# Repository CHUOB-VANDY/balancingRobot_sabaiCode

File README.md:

# balancingRobot_sabaiCode
This hardware development is based on STM32F031C6

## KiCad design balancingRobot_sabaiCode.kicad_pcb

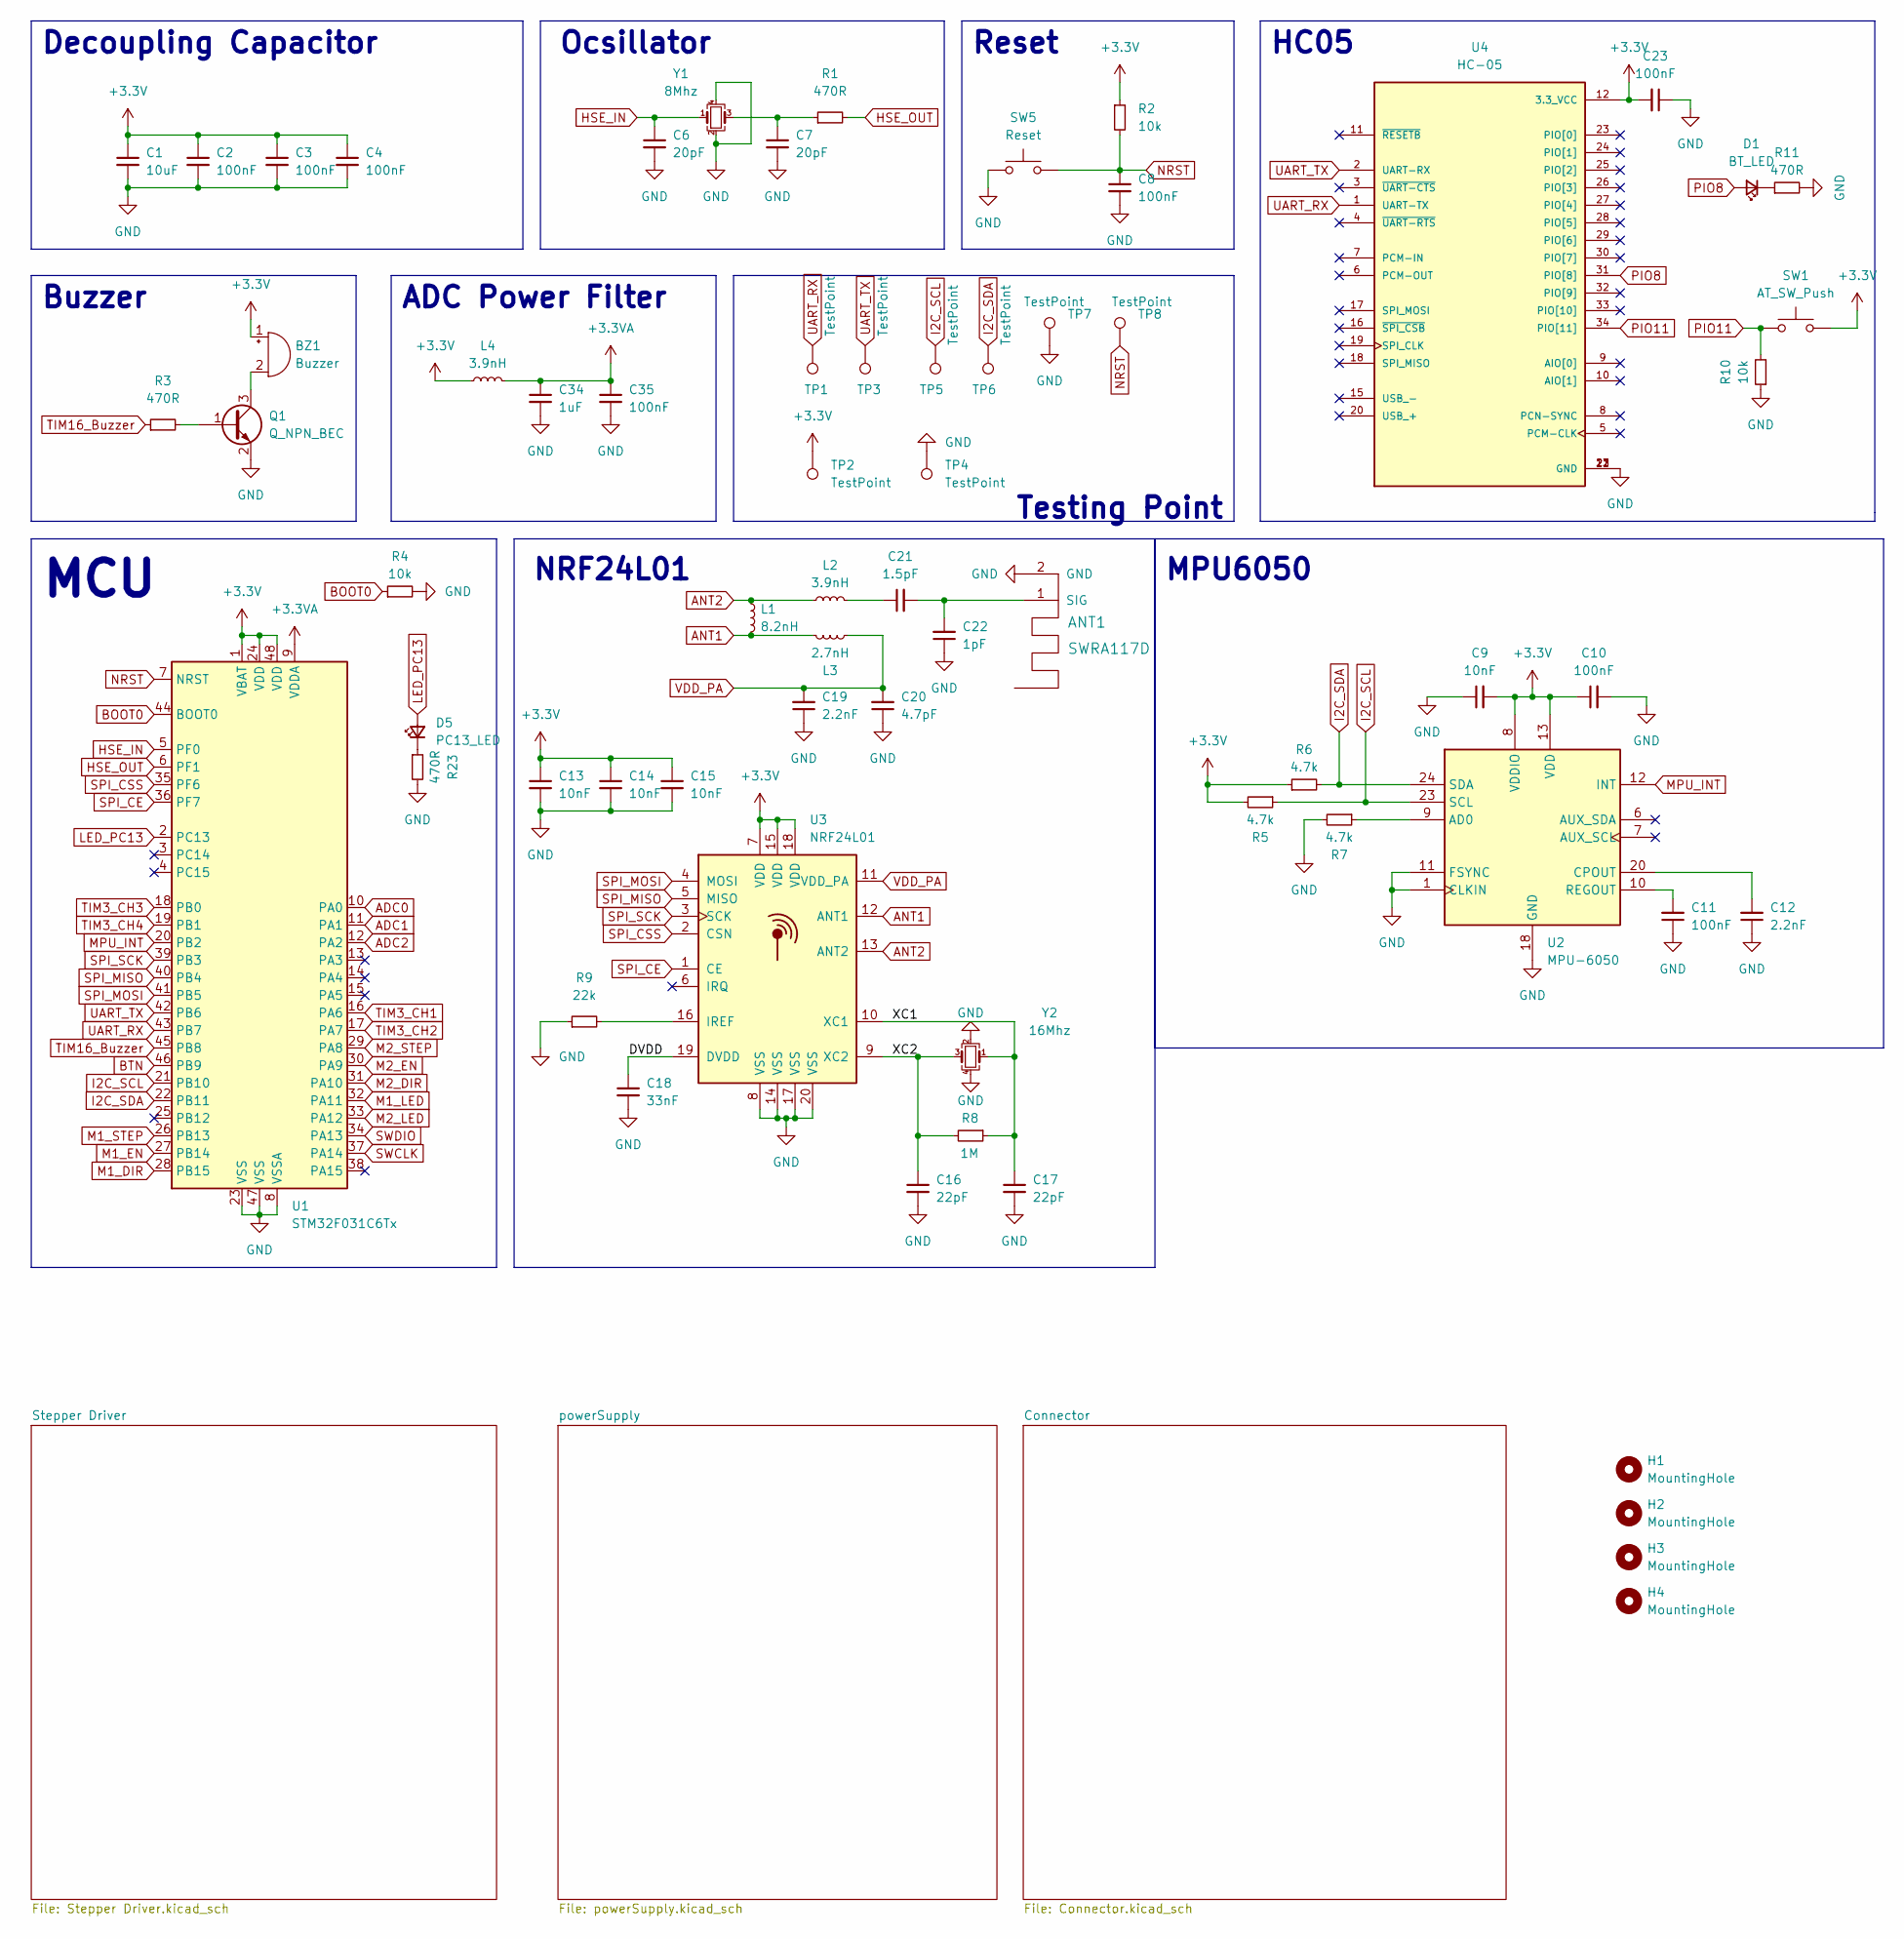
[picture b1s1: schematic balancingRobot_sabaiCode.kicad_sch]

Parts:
ANT1: SWRA117D; Texas_SWRA117D_2.4GHz_Left
BZ1: Buzzer; Buzzer_12x9.5RM7.6
C1: 10uF; C_0805_2012Metric
C2, C3, C4, C8, C10, C11, C23, C35: 100nF; C_0603_1608Metric
C6, C7: 20pF; C_0603_1608Metric
C9, C13, C14, C15: 10nF; C_0603_1608Metric
C12, C19: 2.2nF; C_0603_1608Metric
C16, C17: 22pF; C_0603_1608Metric
C18: 33nF; C_0603_1608Metric
C20: 4.7pF; C_0603_1608Metric
C21: 1.5pF; C_0603_1608Metric
C22: 1pF; C_0603_1608Metric
C34: 1uF; C_0603_1608Metric
D1: BT_LED; LED_0603_1608Metric
D5: PC13_LED; LED_0603_1608Metric
H1, H2, H3, H4: MountingHole; MountingHole_3mm_Pad_Via
L1: 8.2nH; L_0603_1608Metric
L2, L4: 3.9nH; L_0603_1608Metric
L3: 2.7nH; L_0603_1608Metric
Q1: Q_NPN_BEC; SOT-23
R1, R3, R11, R23: 470R; R_0603_1608Metric
R2, R4, R10: 10k; R_0603_1608Metric
R5, R6, R7: 4.7k; R_0603_1608Metric
R8: 1M; R_0603_1608Metric
R9: 22k; R_0603_1608Metric
SW1: AT_SW_Push; SW_SPST_TL3342
SW5: Reset; SW_SPST_TL3342
TP1, TP2, TP3, TP4, TP5, TP6, TP7, TP8: TestPoint; TestPoint_Pad_D1.0mm
U1: STM32F031C6Tx; LQFP-48_7x7mm_P0.5mm
U2: MPU-6050; InvenSense_QFN-24_4x4mm_P0.5mm
U3: NRF24L01; QFN-20-1EP_4x4mm_P0.5mm_EP2.5x2.5mm
U4: HC-05; XCVR_HC-05; PARTREV v1.0
Y1: 8Mhz; Crystal_SMD_3225-4Pin_3.2x2.5mm
Y2: 16Mhz; Crystal_SMD_3225-4Pin_3.2x2.5mm

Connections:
+3.3VA: C34.1, C35.1, L4.2, U1.9 (VDDA)
+3V3: BZ1.1 (-), C1.1, C2.1, C3.1, C4.1, C9.2, C10.1, C13.1, C14.1, C15.1, C23.2, L4.1, R2.1, R5.2, R6.1, SW1.2, TP2.1, U1.1 (VBAT), U1.24 (VDD), U1.48 (VDD), U2.8 (VDDIO), U2.13 (VDD), U3.7 (VDD), U3.15 (VDD), U3.18 (VDD), U4.12 (3.3_VCC); also elsewhere on the board
/DVDD: C18.1, U3.19 (DVDD)
/XC1: C17.1, R8.1, U3.10 (XC1), Y2.1
/XC2: C16.1, R8.2, U3.9 (XC2), Y2.3
ADC0: U1.10 (PA0); also elsewhere on the board
ADC1: U1.11 (PA1); also elsewhere on the board
ADC2: U1.12 (PA2); also elsewhere on the board
ANT1: L1.2, L3.2, U3.12 (ANT1)
ANT2: L1.1, L2.1, U3.13 (ANT2)
BOOT0: R4.1, U1.44 (BOOT0)
BTN: U1.46 (PB9); also elsewhere on the board
GND: ANT1.2 (GND), C1.2, C2.2, C3.2, C4.2, C6.2, C7.2, C8.2, C9.1, C10.2, C11.1, C12.1, C13.2, C14.2, C15.2, C16.2, C17.2, C18.2, C19.1, C20.1, C22.1, C23.1, C34.2, C35.2, Q1.2 (E), R4.2, R7.2, R9.1, R10.1, R11.2, R23.2, SW5.1, TP4.1, TP7.1, U1.8 (VSSA), U1.23 (VSS), U1.47 (VSS), U2.1 (CLKIN), U2.11 (FSYNC), U2.18 (GND), U3.8 (VSS), U3.14 (VSS), U3.17 (VSS), U3.20 (VSS), U4.13 (GND), U4.21 (GND), U4.22 (GND), Y1.2, Y1.4, Y2.2, Y2.4; also elsewhere on the board
HSE_IN: C6.1, U1.5 (PF0), Y1.1
HSE_OUT: R1.2, U1.6 (PF1)
I2C_SCL: R5.1, TP5.1, U1.21 (PB10), U2.23 (SCL); also elsewhere on the board
I2C_SDA: R6.2, TP6.1, U1.22 (PB11), U2.24 (SDA); also elsewhere on the board
LED_PC13: D5.2 (A), U1.2 (PC13)
M1_DIR: U1.28 (PB15); also elsewhere on the board
M1_EN: U1.27 (PB14); also elsewhere on the board
M1_LED: U1.32 (PA11); also elsewhere on the board
M1_STEP: U1.26 (PB13); also elsewhere on the board
M2_DIR: U1.31 (PA10); also elsewhere on the board
M2_EN: U1.30 (PA9); also elsewhere on the board
M2_LED: U1.33 (PA12); also elsewhere on the board
M2_STEP: U1.29 (PA8); also elsewhere on the board
MPU_INT: U1.20 (PB2), U2.12 (INT)
NRST: C8.1, R2.2, SW5.2, TP8.1, U1.7 (NRST)
unnamed: ANT1.1 (SIG), C21.2, C22.2
unnamed: BZ1.2 (+), Q1.3 (C)
unnamed: C7.1, R1.1, Y1.3
unnamed: C11.2, U2.10 (REGOUT)
unnamed: C12.2, U2.20 (CPOUT)
unnamed: C21.1, L2.2
unnamed: D1.1 (K), R11.1
unnamed: D5.1 (K), R23.1
unnamed: Q1.1 (B), R3.2
unnamed: R7.1, U2.9 (AD0)
unnamed: R9.2, U3.16 (IREF)
PIO8: D1.2 (A), U4.31 (PIO[8])
PIO11: R10.2, SW1.1, U4.34 (PIO[11])
SPI_CE: U1.36 (PF7), U3.1 (CE)
SPI_CSS: U1.35 (PF6), U3.2 (CSN)
SPI_MISO: U1.40 (PB4), U3.5 (MISO)
SPI_MOSI: U1.41 (PB5), U3.4 (MOSI)
SPI_SCK: U1.39 (PB3), U3.3 (SCK)
SWCLK: U1.37 (PA14); also elsewhere on the board
SWDIO: U1.34 (PA13); also elsewhere on the board
TIM3_CH1: U1.16 (PA6); also elsewhere on the board
TIM3_CH2: U1.17 (PA7); also elsewhere on the board
TIM3_CH3: U1.18 (PB0); also elsewhere on the board
TIM3_CH4: U1.19 (PB1); also elsewhere on the board
TIM16_Buzzer: R3.1, U1.45 (PB8)
UART_RX: TP1.1, U1.43 (PB7), U4.1 (UART-TX)
UART_TX: TP3.1, U1.42 (PB6), U4.2 (UART-RX)
VDD_PA: C19.2, C20.2, L3.1, U3.11 (VDD_PA)

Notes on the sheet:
Buzzer
NRF24L01
Decoupling Capacitor
HC05
Reset
MCU
Testing Point
MPU6050
ADC Power Filter
Ocsillator

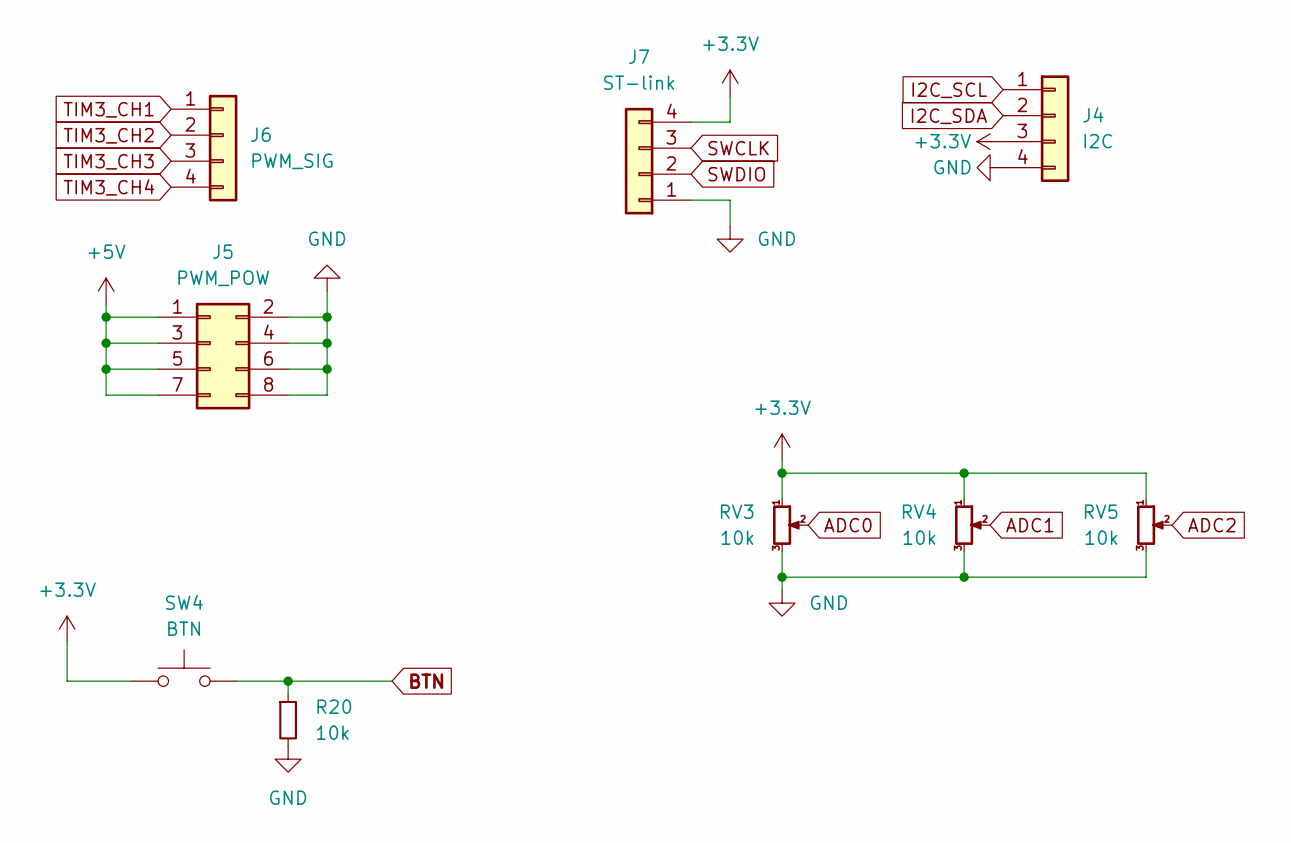
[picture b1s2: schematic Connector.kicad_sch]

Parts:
J4: I2C; ConPadx04
J5: PWM_POW; PinHeader_2x04_P2.54mm_Vertical
J6: PWM_SIG; PinHeader_1x04_P2.54mm_Vertical
J7: ST-link; Molex_KK-254_AE-6410-04A_1x04_P2.54mm_Vertical
R20: 10k; R_0603_1608Metric
RV3, RV4, RV5: 10k; Potentiometer_Vishay_T73YP_Vertical
SW4: BTN; SW_SPST_TL3342

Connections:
+3V3: J4.3, J7.4, RV3.1, RV4.1, RV5.1, SW4.1; also elsewhere on the board
+5V: J5.1, J5.3, J5.5, J5.7; also elsewhere on the board
ADC0: RV3.2; also elsewhere on the board
ADC1: RV4.2; also elsewhere on the board
ADC2: RV5.2; also elsewhere on the board
BTN: R20.1, SW4.2; also elsewhere on the board
GND: J4.4, J5.2, J5.4, J5.6, J5.8, J7.1, R20.2, RV3.3, RV4.3, RV5.3; also elsewhere on the board
I2C_SCL: J4.1; also elsewhere on the board
I2C_SDA: J4.2; also elsewhere on the board
SWCLK: J7.3; also elsewhere on the board
SWDIO: J7.2; also elsewhere on the board
TIM3_CH1: J6.1; also elsewhere on the board
TIM3_CH2: J6.2; also elsewhere on the board
TIM3_CH3: J6.3; also elsewhere on the board
TIM3_CH4: J6.4; also elsewhere on the board

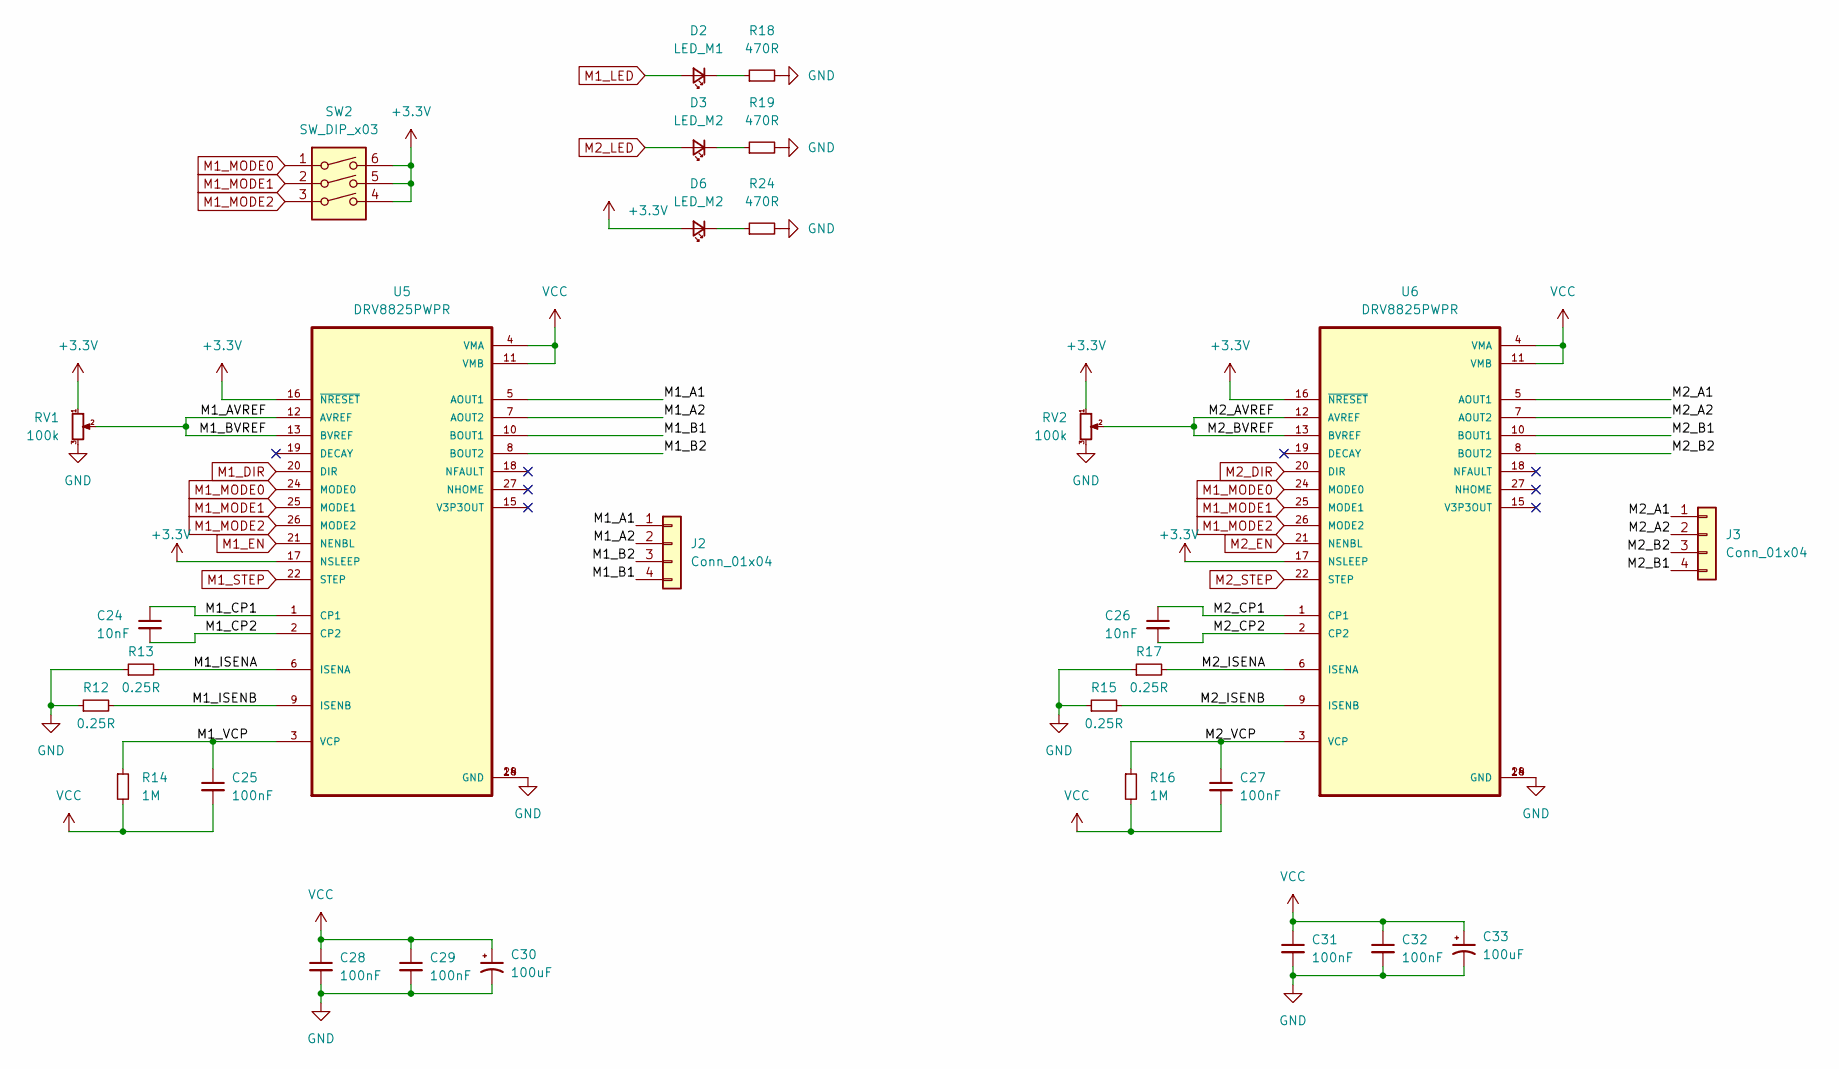
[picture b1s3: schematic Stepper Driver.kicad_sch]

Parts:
C24, C26: 10nF; C_0603_1608Metric
C25, C27, C28, C29, C31, C32: 100nF; C_0603_1608Metric
C30, C33: 100uF; CP_Elec_8x10.5
D2: LED_M1; LED_0603_1608Metric
D3, D6: LED_M2; LED_0603_1608Metric
J2, J3: Conn_01x04; JST_XH_B4B-XH-A_1x04_P2.50mm_Vertical
R12, R13, R15, R17: 0.25R; R_0805_2012Metric
R14, R16: 1M; R_0603_1608Metric
R18, R19, R24: 470R; R_0603_1608Metric
RV1, RV2: 100k; Potentiometer_Bourns_TC33X_Vertical
SW2: SW_DIP_x03; SW_DIP_SPSTx03_Slide_6.7x9.18mm_W8.61mm_P2.54mm_LowProfile
U5, U6: DRV8825PWPR; IC_TPS61196PWPRQ1

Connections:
+3V3: D6.2 (A), RV1.1, RV2.1, SW2.4, SW2.5, SW2.6, U5.16 (~NRESET), U5.17 (NSLEEP), U6.16 (~NRESET), U6.17 (NSLEEP); also elsewhere on the board
/Stepper Driver/M1_A1: J2.1, U5.5 (AOUT1)
/Stepper Driver/M1_A2: J2.2, U5.7 (AOUT2)
/Stepper Driver/M1_AVREF: RV1.2, U5.12 (AVREF), U5.13 (BVREF)
/Stepper Driver/M1_B1: J2.4, U5.10 (BOUT1)
/Stepper Driver/M1_B2: J2.3, U5.8 (BOUT2)
/Stepper Driver/M1_CP1: C24.1, U5.1 (CP1)
/Stepper Driver/M1_CP2: C24.2, U5.2 (CP2)
/Stepper Driver/M1_ISENA: R13.2, U5.6 (ISENA)
/Stepper Driver/M1_ISENB: R12.2, U5.9 (ISENB)
/Stepper Driver/M1_VCP: C25.1, R14.1, U5.3 (VCP)
/Stepper Driver/M2_A1: J3.1, U6.5 (AOUT1)
/Stepper Driver/M2_A2: J3.2, U6.7 (AOUT2)
/Stepper Driver/M2_AVREF: RV2.2, U6.12 (AVREF), U6.13 (BVREF)
/Stepper Driver/M2_B1: J3.4, U6.10 (BOUT1)
/Stepper Driver/M2_B2: J3.3, U6.8 (BOUT2)
/Stepper Driver/M2_CP1: C26.1, U6.1 (CP1)
/Stepper Driver/M2_CP2: C26.2, U6.2 (CP2)
/Stepper Driver/M2_ISENA: R17.2, U6.6 (ISENA)
/Stepper Driver/M2_ISENB: R15.2, U6.9 (ISENB)
/Stepper Driver/M2_VCP: C27.1, R16.1, U6.3 (VCP)
GND: C28.2, C29.2, C30.2, C31.2, C32.2, C33.2, R12.1, R13.1, R15.1, R17.1, R18.2, R19.2, R24.2, RV1.3, RV2.3, U5.14 (GND), U5.28 (GND), U6.14 (GND), U6.28 (GND); also elsewhere on the board
M1_DIR: U5.20 (DIR); also elsewhere on the board
M1_EN: U5.21 (NENBL); also elsewhere on the board
M1_LED: D2.2 (A); also elsewhere on the board
M1_MODE0: SW2.1, U5.24 (MODE0), U6.24 (MODE0)
M1_MODE1: SW2.2, U5.25 (MODE1), U6.25 (MODE1)
M1_MODE2: SW2.3, U5.26 (MODE2), U6.26 (MODE2)
M1_STEP: U5.22 (STEP); also elsewhere on the board
M2_DIR: U6.20 (DIR); also elsewhere on the board
M2_EN: U6.21 (NENBL); also elsewhere on the board
M2_LED: D3.2 (A); also elsewhere on the board
M2_STEP: U6.22 (STEP); also elsewhere on the board
unnamed: D2.1 (K), R18.1
unnamed: D3.1 (K), R19.1
unnamed: D6.1 (K), R24.1
VCC: C25.2, C27.2, C28.1, C29.1, C30.1, C31.1, C32.1, C33.1, R14.2, R16.2, U5.4 (VMA), U5.11 (VMB), U6.4 (VMA), U6.11 (VMB); also elsewhere on the board

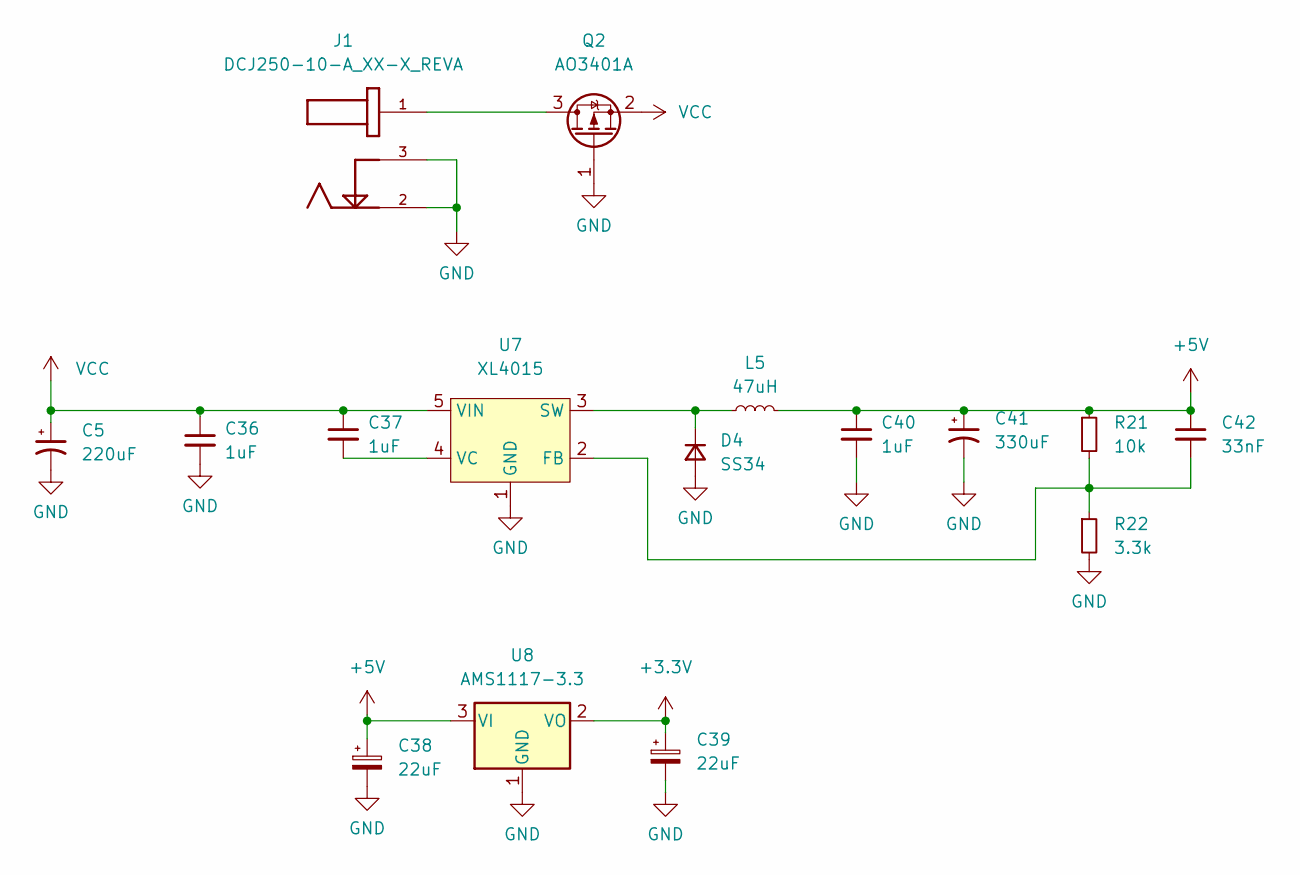
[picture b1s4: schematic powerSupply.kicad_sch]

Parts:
C5: 220uF; CP_Elec_8x10.5
C36, C37, C40: 1uF; C_0603_1608Metric
C38, C39: 22uF; CP_EIA-3216-10_Kemet-I
C41: 330uF; CP_Elec_8x10.5
C42: 33nF; C_0603_1608Metric
D4: SS34; D_SMA
J1: DCJ250-10-A_XX-X_REVA; BarrelJack_Horizontal
L5: 47uH; L_Bourns_SRR1260
Q2: AO3401A; SOT-23
R21: 10k; R_0603_1608Metric
R22: 3.3k; R_0603_1608Metric
U7: XL4015; TO-263-5_TabPin6
U8: AMS1117-3.3; SOT-223-3_TabPin2

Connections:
+3V3: C39.1, U8.2 (VO); also elsewhere on the board
+5V: C38.1, C40.1, C41.1, C42.1, L5.2, R21.1, U8.3 (VI); also elsewhere on the board
GND: C5.2, C36.2, C38.2, C39.2, C40.2, C41.2, D4.2 (A), J1.2, J1.3, Q2.1 (G), R22.2, U7.1 (GND), U8.1 (GND); also elsewhere on the board
unnamed: C37.2, U7.4 (VC)
unnamed: C42.2, R21.2, R22.1, U7.2 (FB)
unnamed: D4.1 (K), L5.1, U7.3 (SW)
unnamed: J1.1, Q2.3 (D)
VCC: C5.1, C36.1, C37.1, Q2.2 (S), U7.5 (VIN); also elsewhere on the board

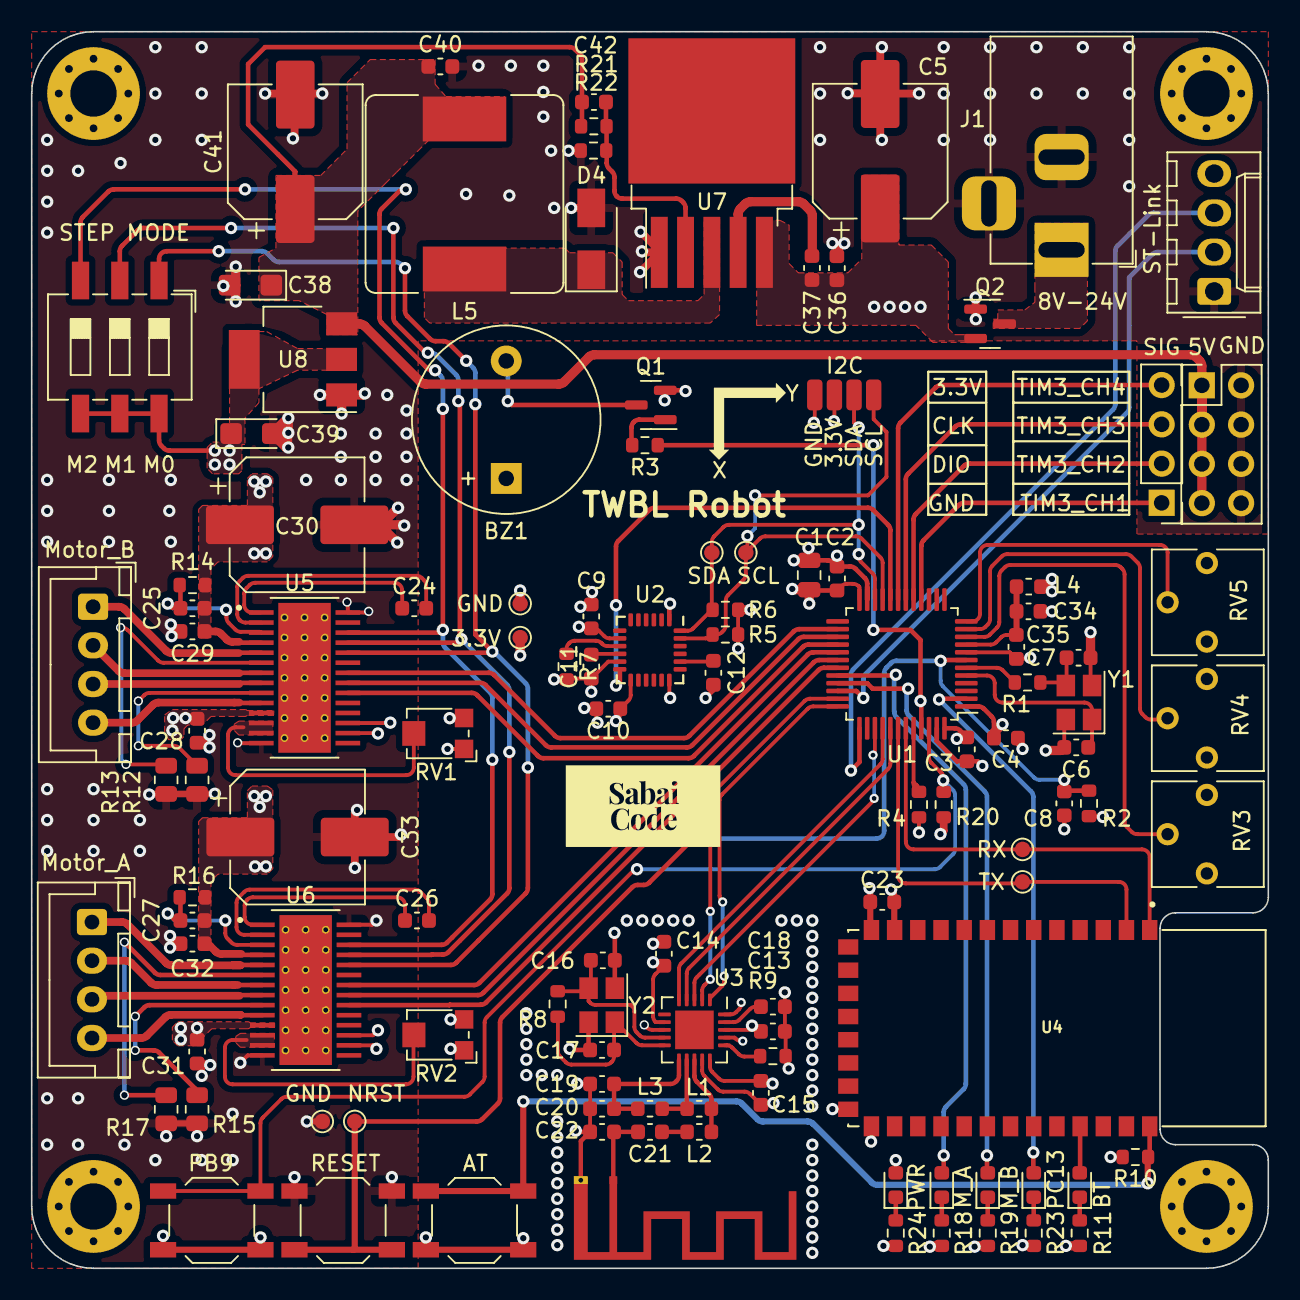
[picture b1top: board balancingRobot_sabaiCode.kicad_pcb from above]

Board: 4 copper layers, 80.0 x 80.0 mm, 119 parts (0 on the bottom side), 88 nets.

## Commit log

2022-08-19 add file
